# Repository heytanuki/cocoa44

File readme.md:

# 44% Cocoa

A choc-spaced, splittable 40 with hazard stripes across the top.

The 44% Cocoa was designed and sized to be under the 100mm^2 limit for free fabrication thru Allpcb. It is a little wider than 100mm wide, but that didn't seem to affect it being free!

### One small issue...

This has mounting holes directly under the top-left and top-right switches. What that means is that likely you will need to either use countersunk screws on those holes (the kind that have a conical head shape that's wider at the top), or change the size of the board to move those holes out to the side.

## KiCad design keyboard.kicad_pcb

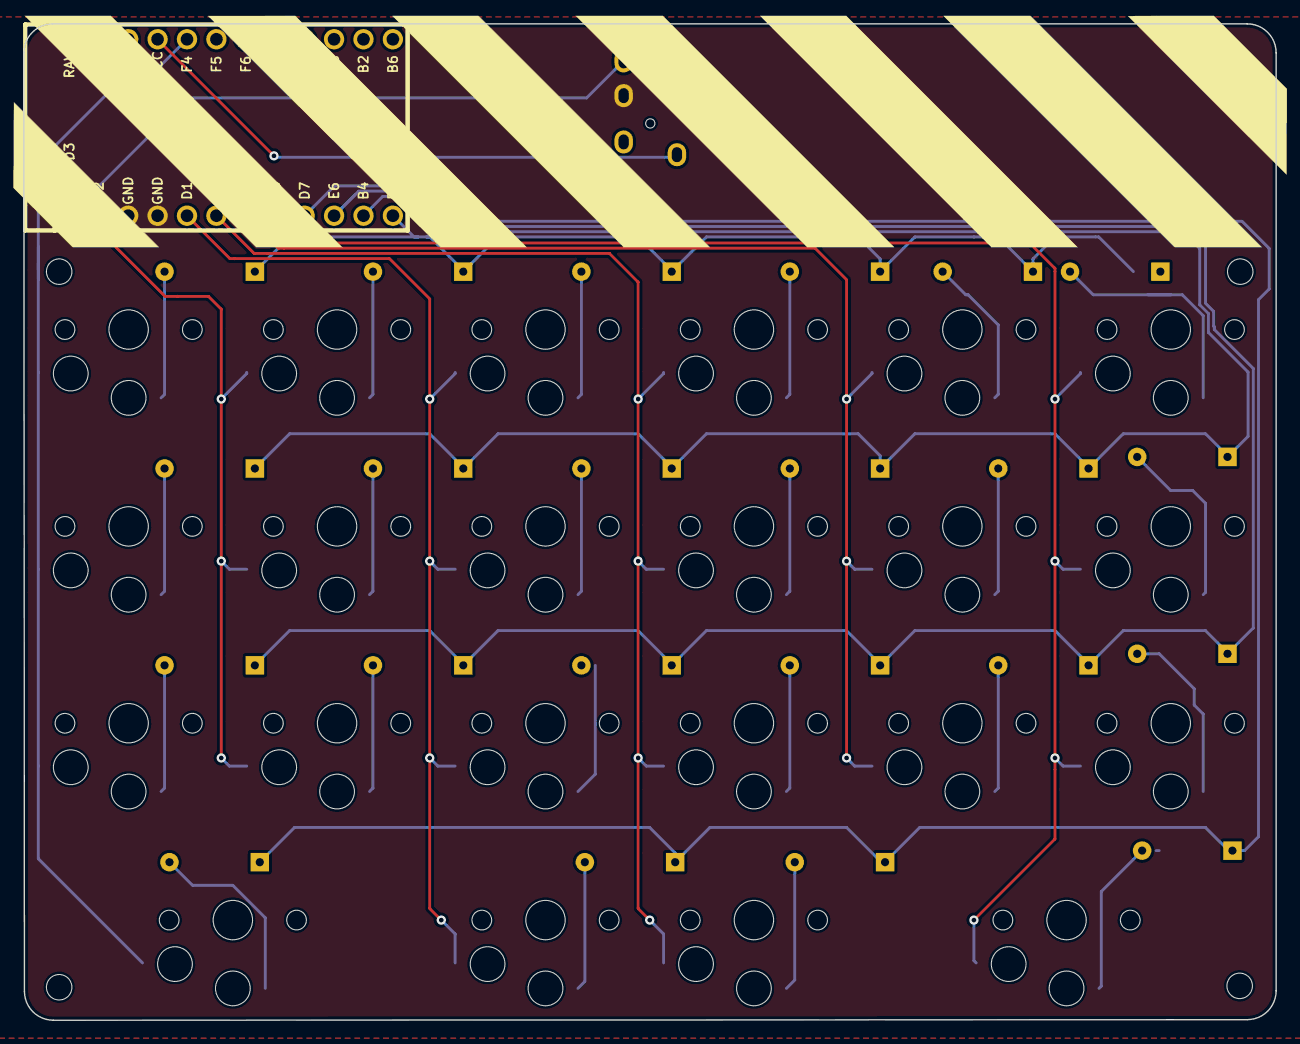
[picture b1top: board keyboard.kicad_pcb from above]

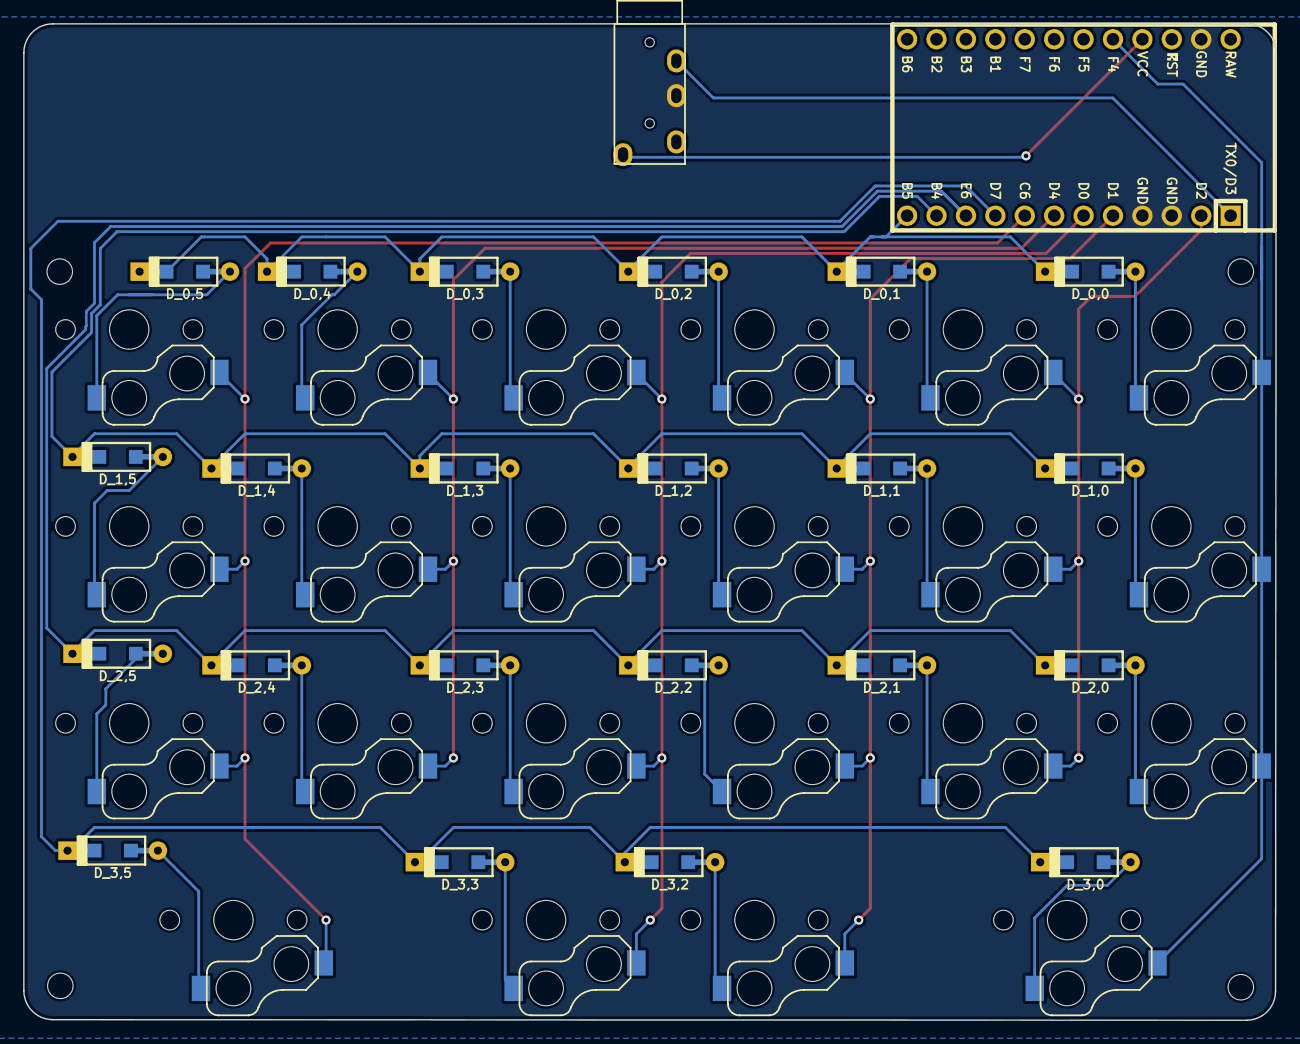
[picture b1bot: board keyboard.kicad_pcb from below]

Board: 2 copper layers, 108.1 x 86.1 mm, 46 parts (23 on the bottom side), 35 nets.

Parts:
D_0,0, D_0,1, D_0,2, D_0,3, D_0,4, D_0,5, D_1,0, D_1,1, D_1,2, D_1,3, D_1,4, D_1,5, D_2,0, D_2,1, D_2,2, D_2,3, D_2,4, D_2,5, D_3,0, D_3,2, D_3,3, D_3,5: D; D_SOD123_axial
K3,2: KEYSW; Choc-1u
K_0,0, K_0,1, K_0,2, K_0,3, K_0,4, K_0,5, K_1,0, K_1,1, K_1,2, K_1,3, K_1,4, K_1,5, K_2,0, K_2,1, K_2,2, K_2,3, K_2,4, K_2,5, K_3,3: KEYSW; Choc-1u
K_3,0, K_3,5: KEYSW; Choc-2u
U1: ProMicro; ArduinoProMicro
U2: TRRS; TRRS-PJ-320A

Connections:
GND: U1.3, U1.4, U1.23, U2.3
unnamed: D_0,0.2, K_0,0.2
unnamed: D_0,1.2, K_0,1.2
unnamed: D_0,2.2, K_0,2.2
unnamed: D_0,3.2, K_0,3.2
unnamed: D_0,4.2, K_0,4.2
unnamed: D_0,5.2, K_0,5.2
unnamed: D_1,0.2, K_1,0.2
unnamed: D_1,1.2, K_1,1.2
unnamed: D_1,2.2, K_1,2.2
unnamed: D_1,3.2, K_1,3.2
unnamed: D_1,4.2, K_1,4.2
unnamed: D_1,5.2, K_1,5.2
unnamed: D_2,0.2, K_2,0.2
unnamed: D_2,1.2, K_2,1.2
unnamed: D_2,2.2, K_2,2.2
unnamed: D_2,3.2, K_2,3.2
unnamed: D_2,4.2, K_2,4.2
unnamed: D_2,5.2, K_2,5.2
unnamed: D_3,0.2, K_3,0.2
unnamed: D_3,2.2, K3,2.2
unnamed: D_3,3.2, K_3,3.2
unnamed: D_3,5.2, K_3,5.2
unnamed: U1.1, U2.4
unnamed: U1.21, U2.1
col0: K_0,0.1, K_1,0.1, K_2,0.1, K_3,0.1, U1.20
col1: K_0,1.1, K_1,1.1, K_2,1.1, U1.2
col2: K3,2.1, K_0,2.1, K_1,2.1, K_2,2.1, U1.5
col3: K_0,3.1, K_1,3.1, K_2,3.1, K_3,3.1, U1.6
col4: K_0,4.1, K_1,4.1, K_2,4.1, U1.7
col5: K_0,5.1, K_1,5.1, K_2,5.1, K_3,5.1, U1.8
row0: D_0,0.1, D_0,1.1, D_0,2.1, D_0,3.1, D_0,4.1, D_0,5.1, U1.12
row1: D_1,0.1, D_1,1.1, D_1,2.1, D_1,3.1, D_1,4.1, D_1,5.1, U1.11
row2: D_2,0.1, D_2,1.1, D_2,2.1, D_2,3.1, D_2,4.1, D_2,5.1, U1.10
row3: D_3,0.1, D_3,2.1, D_3,3.1, D_3,5.1, U1.9

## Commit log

2021-10-06 Uploading everything
2021-10-06 Add qmk code
